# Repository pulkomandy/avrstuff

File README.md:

Various AVR (and other) stuff
=============================

This slightly messy repo is home to many of my electronics hacks and projects.

A wiki describing most of the stuff is at http://pulkomandy.tk/projects/avrstuff/ .

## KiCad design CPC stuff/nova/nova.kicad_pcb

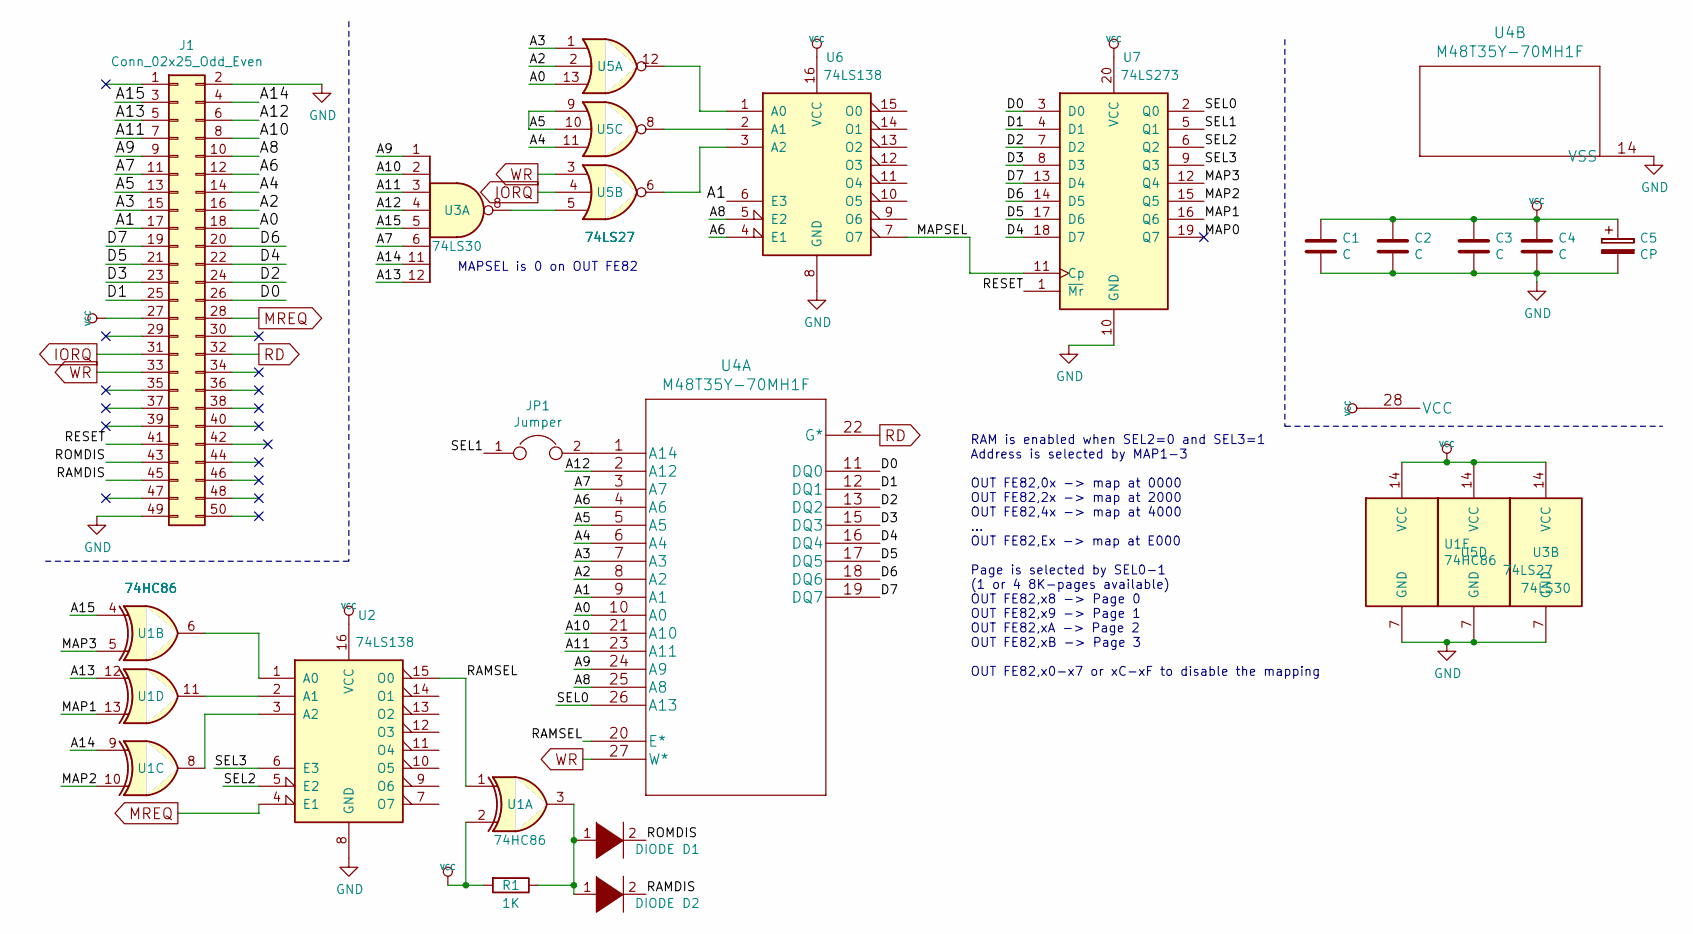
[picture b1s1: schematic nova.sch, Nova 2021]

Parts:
C1, C2, C3, C4: C; C_1206_3216Metric
C5: CP; CP_Radial_D5.0mm_P2.50mm
D1, D2: DIODE; D_SOD-123F
J1: Conn_02x25_Odd_Even; PinHeader_2x25_P2.54mm_Vertical
JP1: Jumper; SolderJumper-2_P1.3mm_Open_RoundedPad1.0x1.5mm
R1: 1K; R_0805_2012Metric
U1: 74HC86; SOIC-14_3.9x8.7mm_P1.27mm
U2, U6: 74LS138; SOIC-16_3.9x9.9mm_P1.27mm
U3: 74LS30; SOIC-14_3.9x8.7mm_P1.27mm
U4: M48T35Y-70MH1F
U5: 74LS27; SOIC-14_3.9x8.7mm_P1.27mm
U7: 74LS273; SOIC-20W_7.5x12.8mm_P1.27mm

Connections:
/A0: J1.18, U4.10 (A0), U5.13
/A1: J1.17, U4.9 (A1), U6.6 (E3)
/A2: J1.16, U4.8 (A2), U5.2
/A3: J1.15, U4.7 (A3), U5.1
/A4: J1.14, U4.6 (A4), U5.11
/A5: J1.13, U4.5 (A5), U5.9, U5.10
/A6: J1.12, U4.4 (A6), U6.4 (E1)
/A7: J1.11, U3.6, U4.3 (A7)
/A8: J1.10, U4.25 (A8), U6.5 (E2)
/A9: J1.9, U3.1, U4.24 (A9)
/A10: J1.8, U3.2, U4.21 (A10)
/A11: J1.7, U3.3, U4.23 (A11)
/A12: J1.6, U3.4, U4.2 (A12)
/A13: J1.5, U1.12, U3.12
/A14: J1.4, U1.9, U3.11
/A15: J1.3, U1.4, U3.5
/D0: J1.26, U4.11 (DQ0), U7.3 (D0)
/D1: J1.25, U4.12 (DQ1), U7.4 (D1)
/D2: J1.24, U4.13 (DQ2), U7.7 (D2)
/D3: J1.23, U4.15 (DQ3), U7.8 (D3)
/D4: J1.22, U4.16 (DQ4), U7.18 (D7)
/D5: J1.21, U4.17 (DQ5), U7.17 (D6)
/D6: J1.20, U4.18 (DQ6), U7.14 (D5)
/D7: J1.19, U4.19 (DQ7), U7.13 (D4)
/MAP1: U1.13, U7.16 (Q6)
/MAP2: U1.10, U7.15 (Q5)
/MAP3: U1.5, U7.12 (Q4)
/MAPSEL: U6.7 (O7), U7.11 (Cp)
/RAMDIS: D2.2 (A), J1.45
/RAMSEL: U1.1, U2.15 (O0), U4.20 (E*)
/RESET: J1.41, U7.1 (~Mr)
/ROMDIS: D1.2 (A), J1.43
/SEL0: U4.26 (A13), U7.2 (Q0)
/SEL1: JP1.1, U7.5 (Q1)
/SEL2: U2.5 (E2), U7.6 (Q2)
/SEL3: U2.6 (E3), U7.9 (Q3)
GND: C1.2, C2.2, C3.2, C4.2, C5.2, J1.2, J1.49, U1.7 (GND), U2.8 (GND), U3.7 (GND), U4.14 (VSS), U5.7 (GND), U6.8 (GND), U7.10 (GND)
IORQ: J1.31, U5.4
MREQ: J1.28, U2.4 (E1)
unnamed: D1.1 (K), D2.1 (K), R1.1, U1.3
unnamed: JP1.2, U4.1 (A14)
unnamed: U1.6, U2.1 (A0)
unnamed: U1.8, U2.3 (A2)
unnamed: U1.11, U2.2 (A1)
unnamed: U3.8, U5.5
unnamed: U5.6, U6.3 (A2)
unnamed: U5.8, U6.2 (A1)
unnamed: U5.12, U6.1 (A0)
RD: J1.32, U4.22 (G*)
VCC: C1.1, C2.1, C3.1, C4.1, C5.1, J1.27, R1.2, U1.2, U1.14 (VCC), U2.16 (VCC), U3.14 (VCC), U4.28 (VCC), U5.14 (VCC), U6.16 (VCC), U7.20 (VCC)
WR: J1.33, U4.27 (W*), U5.3

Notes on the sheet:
MAPSEL is 0 on OUT FE82
RAM is enabled when SEL2=0 and SEL3=1 Address is selected by MAP1-3 OUT FE82,0x -> map at 0000 OUT FE82,2x -> map at 2000 OUT FE82,4x -> map at 4000 ... OUT FE82,Ex -> map at E000 Page is selected by SEL0-1 (1 or 4 8K-pages available) OUT FE82,x8 -> Page 0 OUT FE82,x9 -> Page 1 OUT FE82,xA -> Page 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

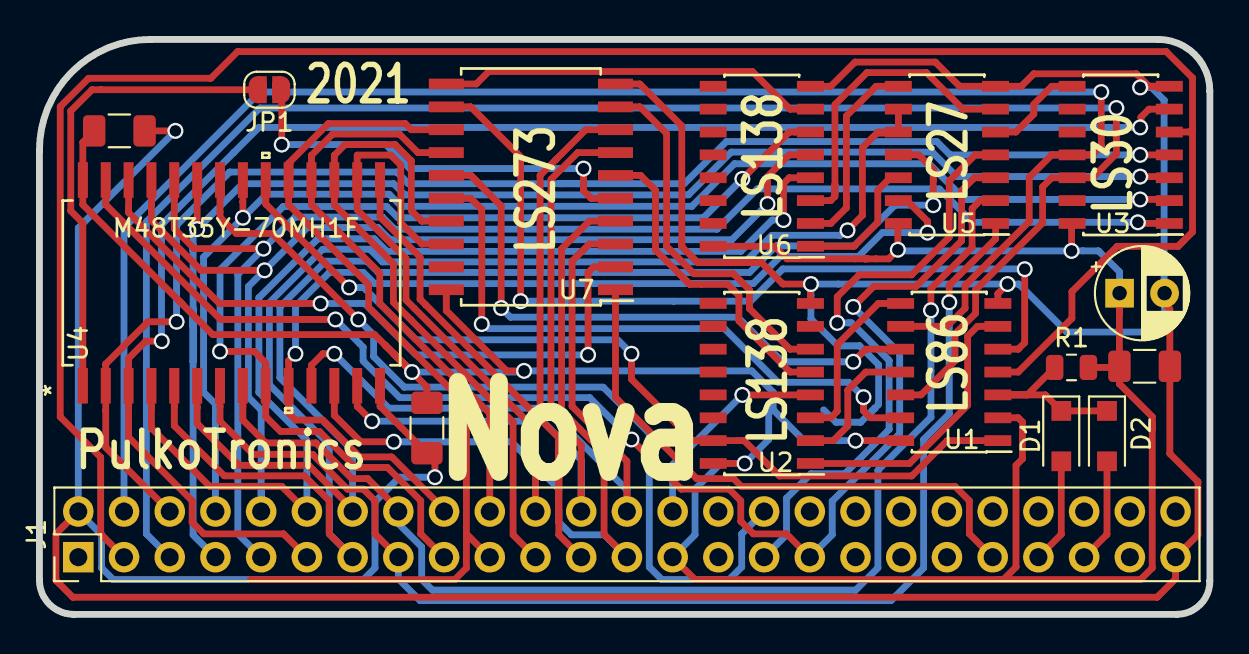
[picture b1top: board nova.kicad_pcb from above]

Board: 2 copper layers, 65.0 x 31.9 mm, 17 parts (0 on the bottom side), 51 nets.

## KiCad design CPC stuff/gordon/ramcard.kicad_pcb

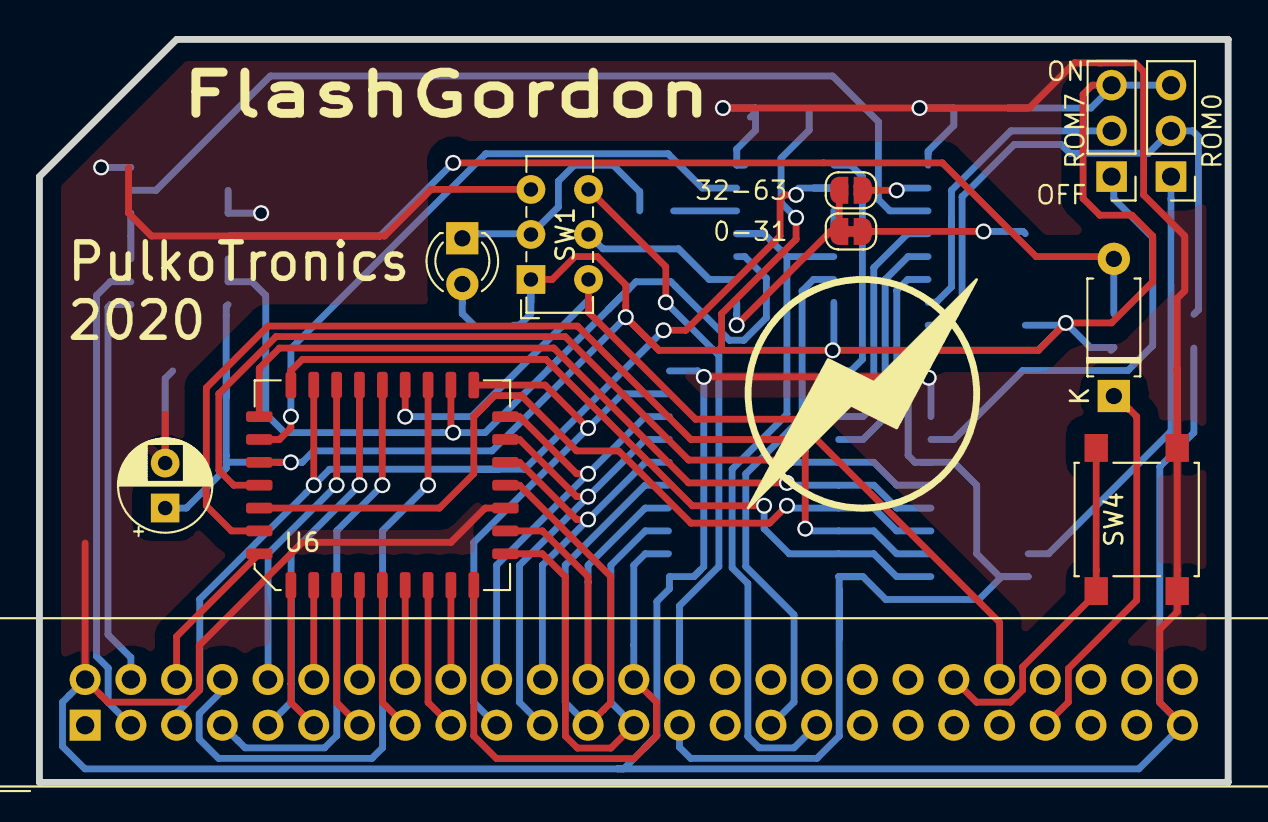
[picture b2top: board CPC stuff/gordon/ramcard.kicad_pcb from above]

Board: 2 copper layers, 66.0 x 41.3 mm, 23 parts (0 on the bottom side), 58 nets.

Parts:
1K, 1K#2: 1KR; R_0805_2012Metric
10K: 10KR; R_0805_2012Metric
220: 220R; R_0805_2012Metric
C2, C3, C4: C; C_1206_3216Metric_Pad1.42x1.75mm_HandSolder
C5: CP1; CP_Radial_D5.0mm_P2.50mm
D1: LED; LED_D3.0mm
D13: DIODE; D_A-405_P7.62mm_Horizontal
JP1, JP2: Jumper_3_Open; PinHeader_1x03_P2.54mm_Vertical
JP3: Jumper_NC_Small; SolderJumper-2_P1.3mm_Bridged_RoundedPad1.0x1.5mm
JP4: Jumper_NO_Small; SolderJumper-2_P1.3mm_Open_RoundedPad1.0x1.5mm
P1: CONN_25X2; IDC-Header_2x25_P2.54mm_Vertical
SW1: WRITE; SW_E-Switch_EG1271_DPDT
SW4: SW_PUSH; SW_SPST_B3S-1000
U1: 74LS574; SOIC-20W_7.5x12.8mm_P1.27mm
U2: 74LS32; SOIC-14_3.9x8.7mm_P1.27mm
U3, U5: 74LS138; SOIC-16_3.9x9.9mm_P1.27mm
U4: 74LS00; SOIC-14_3.9x8.7mm_P1.27mm
U6: 29C040; PLCC-32_11.4x14.0mm_P1.27mm

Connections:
//CE: U2.3, U4.12, U4.13, U6.22
//WE: U2.6, U6.31
/A0: P1.18, U6.12
/A1: P1.17, U6.11
/A2: P1.16, U6.10
/A3: P1.15, U6.9
/A4: P1.14, U6.8
/A5: P1.13, U6.7
/A6: P1.12, U6.6
/A7: P1.11, U6.5
/A8: P1.10, U6.27
/A9: P1.9, U6.26
/A10: P1.8, U6.23
/A11: P1.7, U6.25
/A12: P1.6, U6.4
/A13: P1.5, U2.9, U6.28
/A14: P1.4, U4.1
/A14A15: U4.6, U5.6
/A15: P1.3, U4.2
/BUSRESET: P1.40, SW4.1
/D0: P1.26, U1.2, U6.13
/D1: P1.25, U1.3, U6.14
/D2: P1.24, U1.4, U6.15
/D3: P1.23, U1.5, U6.17
/D4: P1.22, U1.6, U6.18
/D5: P1.21, U1.7, U6.19
/D6: P1.20, U1.8, U6.20
/D7: P1.19, U1.9, U6.21
/Q0: U1.19, U3.1, U6.29
/Q1: U1.18, U3.2, U6.3
/Q2: U1.17, U3.3, U6.2
/Q3: U1.16, U3.4, U6.30
/Q4: U1.15, U3.5, U6.1
/Q5: U1.14, U5.3
/Q6: U1.13, U5.4
/Q7: U1.12, U5.5
/R0EN: 10K.1, JP2.2, U5.1
/R7EN: JP1.2, U5.2
/RDWR: SW1.5, U2.2
/ROMACC: JP3.2, JP4.2, U2.1
GND: 10K.2, C2.2, C3.2, C4.2, C5.2, P1.2, P1.49, SW1.3, SW4.2, U1.1, U1.10, U2.7, U3.8, U4.7, U4.9, U4.10, U5.8, U6.16
IORQ: P1.31, U2.13
MREQ: P1.28, SW1.6
unnamed: 220.1, D1.1, SW1.2
unnamed: 1K.2, D1.2
unnamed: 1K#2.1, D13.2, U4.11
unnamed: JP1.1, U3.7
unnamed: JP2.1, U3.15
unnamed: JP3.1, U5.12
unnamed: JP4.1, U5.7
unnamed: 220.2, U2.5
unnamed: U2.10, U2.11
unnamed: U4.3, U4.4, U4.5
ROMDIS: D13.1, P1.43
ROMEN: P1.42, SW1.4, U6.24
ROMSEL: U1.11, U2.8
VCC: 1K.1, 1K#2.2, C2.1, C3.1, C4.1, C5.1, JP1.3, JP2.3, P1.27, SW1.1, U1.20, U2.14, U3.6, U3.16, U4.14, U5.16, U6.32
WR: P1.33, U2.4, U2.12

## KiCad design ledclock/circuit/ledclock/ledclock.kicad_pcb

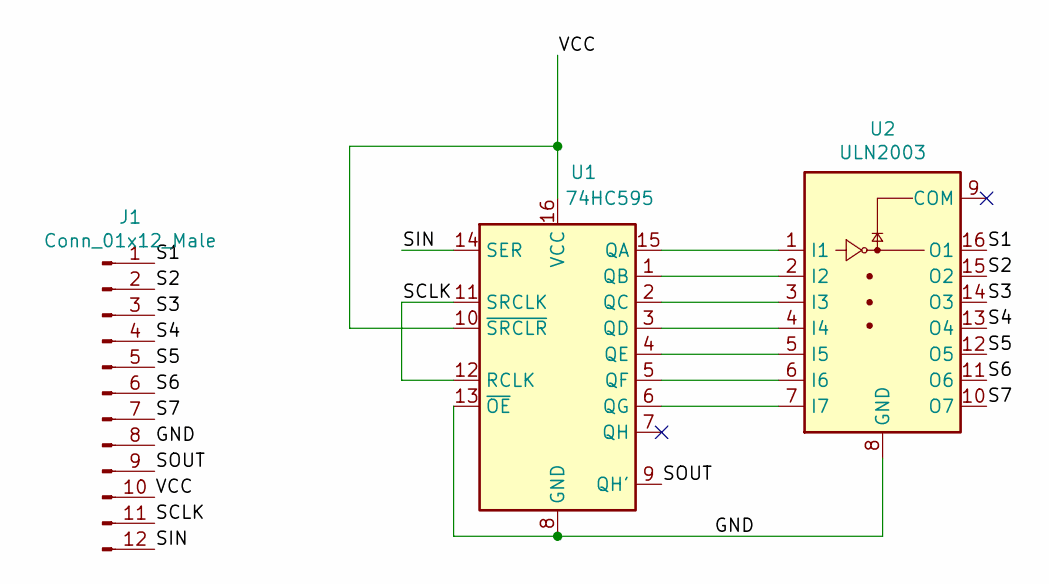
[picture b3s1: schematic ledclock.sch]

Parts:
J1: Conn_01x12_Male; TE_MicroMatch_215750-0016_2x08_P1.27mm_Vertical
U1: 74HC595; DIP-16_W7.62mm
U2: ULN2003; SOIC-16_3.9x9.9mm_P1.27mm

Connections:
/GND: J1.8, U1.8 (GND), U1.13 (~OE), U2.8 (GND)
/S1: J1.1, U2.16 (O1)
/S2: J1.2, U2.15 (O2)
/S3: J1.3, U2.14 (O3)
/S4: J1.4, U2.13 (O4)
/S5: J1.5, U2.12 (O5)
/S6: J1.6, U2.11 (O6)
/S7: J1.7, U2.10 (O7)
/SCLK: J1.11, U1.11 (SRCLK), U1.12 (RCLK)
/SIN: J1.12, U1.14 (SER)
/SOUT: J1.9, U1.9 (QH')
/VCC: J1.10, U1.10 (~SRCLR), U1.16 (VCC)
unnamed: U1.1 (QB), U2.2 (I2)
unnamed: U1.2 (QC), U2.3 (I3)
unnamed: U1.3 (QD), U2.4 (I4)
unnamed: U1.4 (QE), U2.5 (I5)
unnamed: U1.5 (QF), U2.6 (I6)
unnamed: U1.6 (QG), U2.7 (I7)
unnamed: U1.15 (QA), U2.1 (I1)

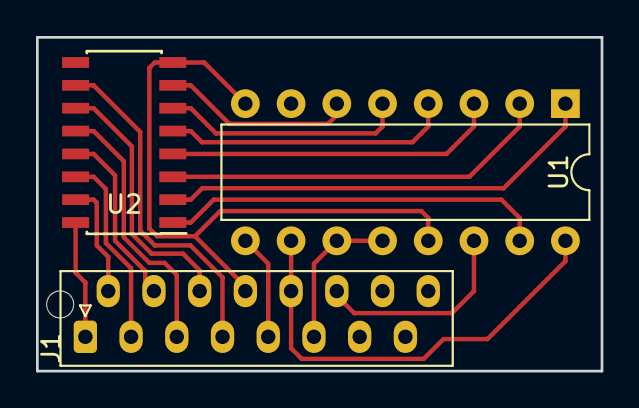
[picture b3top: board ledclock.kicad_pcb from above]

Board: 2 copper layers, 31.4 x 18.5 mm, 3 parts (0 on the bottom side), 19 nets.

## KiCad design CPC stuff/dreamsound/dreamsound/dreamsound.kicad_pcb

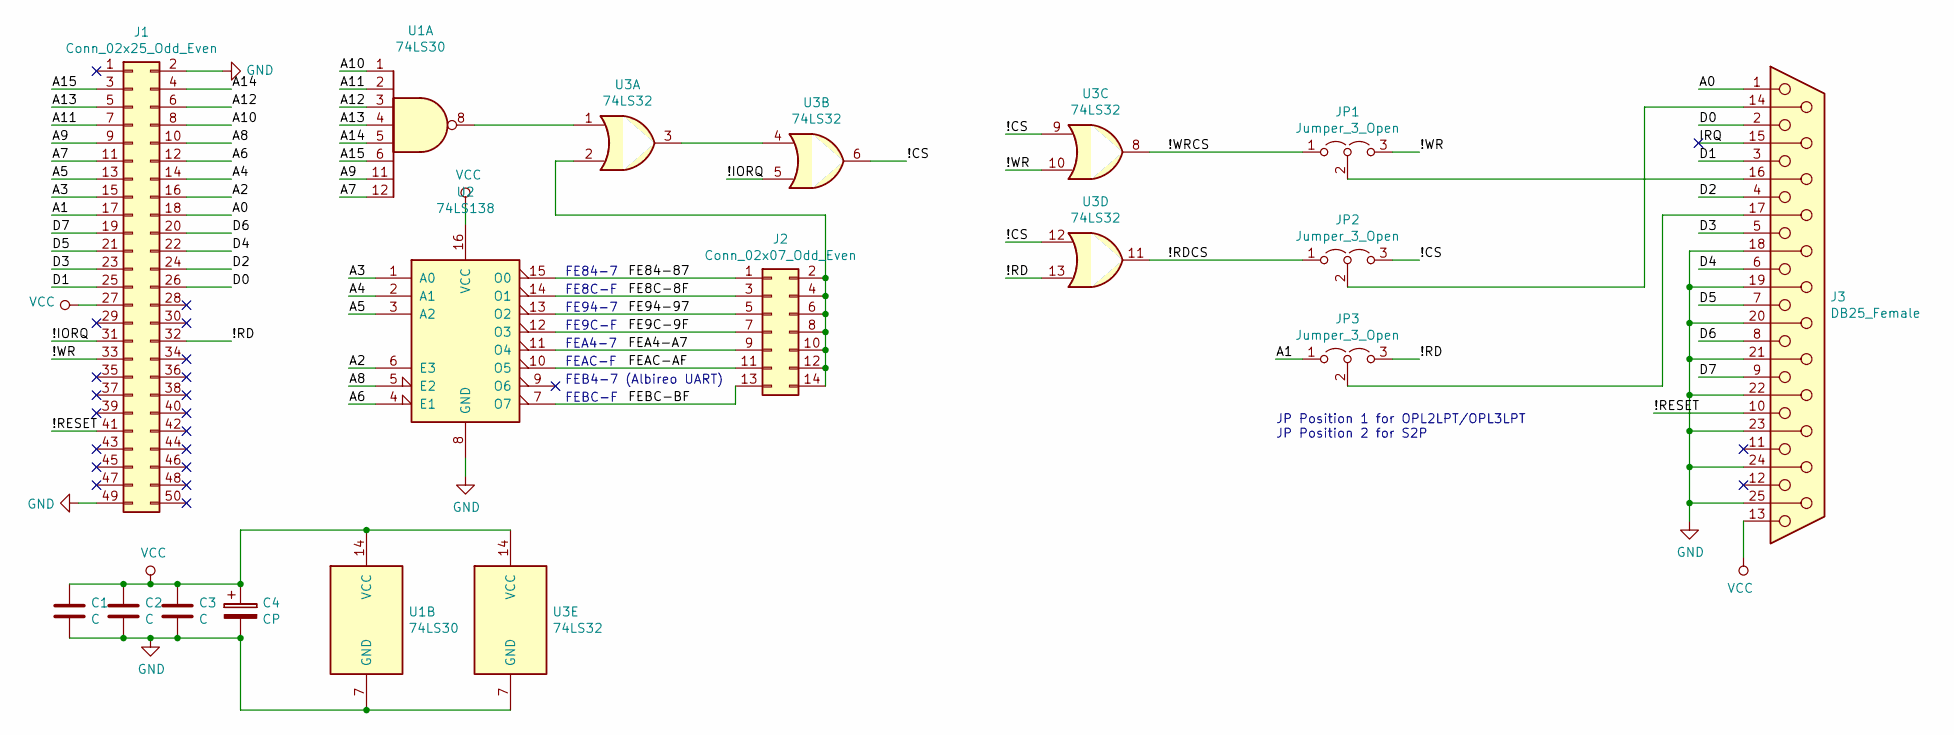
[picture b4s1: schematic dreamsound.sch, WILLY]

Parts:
C1, C2, C3: C; C_1206_3216Metric_Pad1.42x1.75mm_HandSolder
C4: CP; CP_Radial_D5.0mm_P2.50mm
J1: Conn_02x25_Odd_Even; IDC-Header_2x25_P2.54mm_Vertical
J2: Conn_02x07_Odd_Even; PinHeader_2x07_P2.54mm_Vertical
J3: DB25_Female; DSUB-25_Female_Horizontal_P2.77x2.84mm_EdgePinOffset4.94mm_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
JP1, JP2, JP3: Jumper_3_Open; PinHeader_1x03_P2.54mm_Vertical
U1: 74LS30; SOIC-14_3.9x8.7mm_P1.27mm
U2: 74LS138; SOIC-16_3.9x9.9mm_P1.27mm
U3: 74LS32; SOIC-14_3.9x8.7mm_P1.27mm

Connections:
/!CS: JP2.3 (B), U3.6, U3.9, U3.12
/!IORQ: J1.31, U3.5
/!RD: J1.32, JP3.3 (B), U3.13
/!RDCS: JP2.1 (A), U3.11
/!RESET: J1.41, J3.10
/!WR: J1.33, JP1.3 (B), U3.10
/!WRCS: JP1.1 (A), U3.8
/A0: J1.18, J3.1
/A1: J1.17, JP3.1 (A)
/A2: J1.16, U2.6 (E3)
/A3: J1.15, U2.1 (A0)
/A4: J1.14, U2.2 (A1)
/A5: J1.13, U2.3 (A2)
/A6: J1.12, U2.4 (E1)
/A7: J1.11, U1.12
/A8: J1.10, U2.5 (E2)
/A9: J1.9, U1.11
/A10: J1.8, U1.1
/A11: J1.7, U1.2
/A12: J1.6, U1.3
/A13: J1.5, U1.4
/A14: J1.4, U1.5
/A15: J1.3, U1.6
/D0: J1.26, J3.2
/D1: J1.25, J3.3
/D2: J1.24, J3.4
/D3: J1.23, J3.5
/D4: J1.22, J3.6
/D5: J1.21, J3.7
/D6: J1.20, J3.8
/D7: J1.19, J3.9
/FE8C-8F: J2.3, U2.14 (O1)
/FE9C-9F: J2.7, U2.12 (O3)
/FE84-87: J2.1, U2.15 (O0)
/FE94-97: J2.5, U2.13 (O2)
/FEA4-A7: J2.9, U2.11 (O4)
/FEAC-AF: J2.11, U2.10 (O5)
/FEBC-BF: J2.13, U2.7 (O7)
GND: C1.2, C2.2, C3.2, C4.2, J1.2, J1.49, J3.18, J3.19, J3.20, J3.21, J3.22, J3.23, J3.24, J3.25, U1.7 (GND), U2.8 (GND), U3.7 (GND)
unnamed: J2.2, J2.4, J2.6, J2.8, J2.10, J2.12, J2.14, U3.2
unnamed: J3.14, JP2.2 (C)
unnamed: J3.16, JP1.2 (C)
unnamed: J3.17, JP3.2 (C)
unnamed: U1.8, U3.1
unnamed: U3.3, U3.4
VCC: C1.1, C2.1, C3.1, C4.1, J1.27, J3.13, U1.14 (VCC), U2.16 (VCC), U3.14 (VCC)

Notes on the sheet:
FE84-7
FE8C-F
FE94-7
FE9C-F
FEA4-7
FEAC-F
FEB4-7 (Albireo UART)
FEBC-F
JP Position 1 for OPL2LPT/OPL3LPT JP Position 2 for S2P

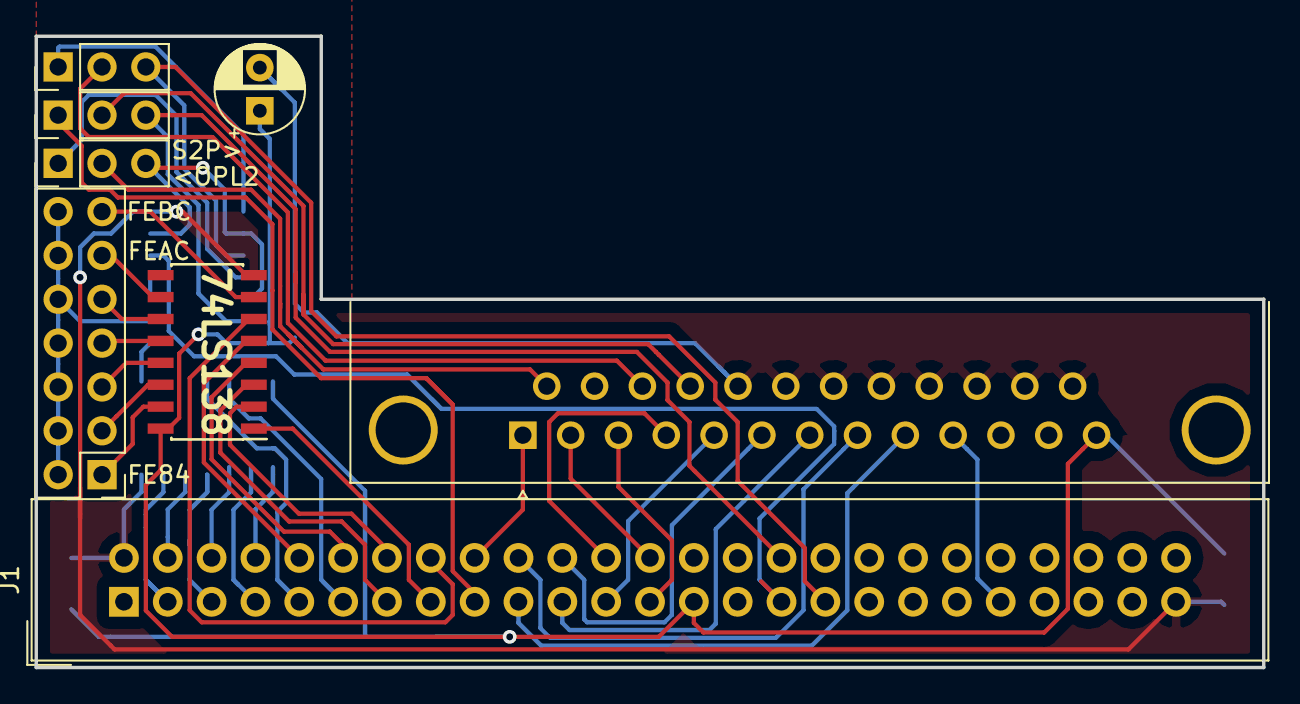
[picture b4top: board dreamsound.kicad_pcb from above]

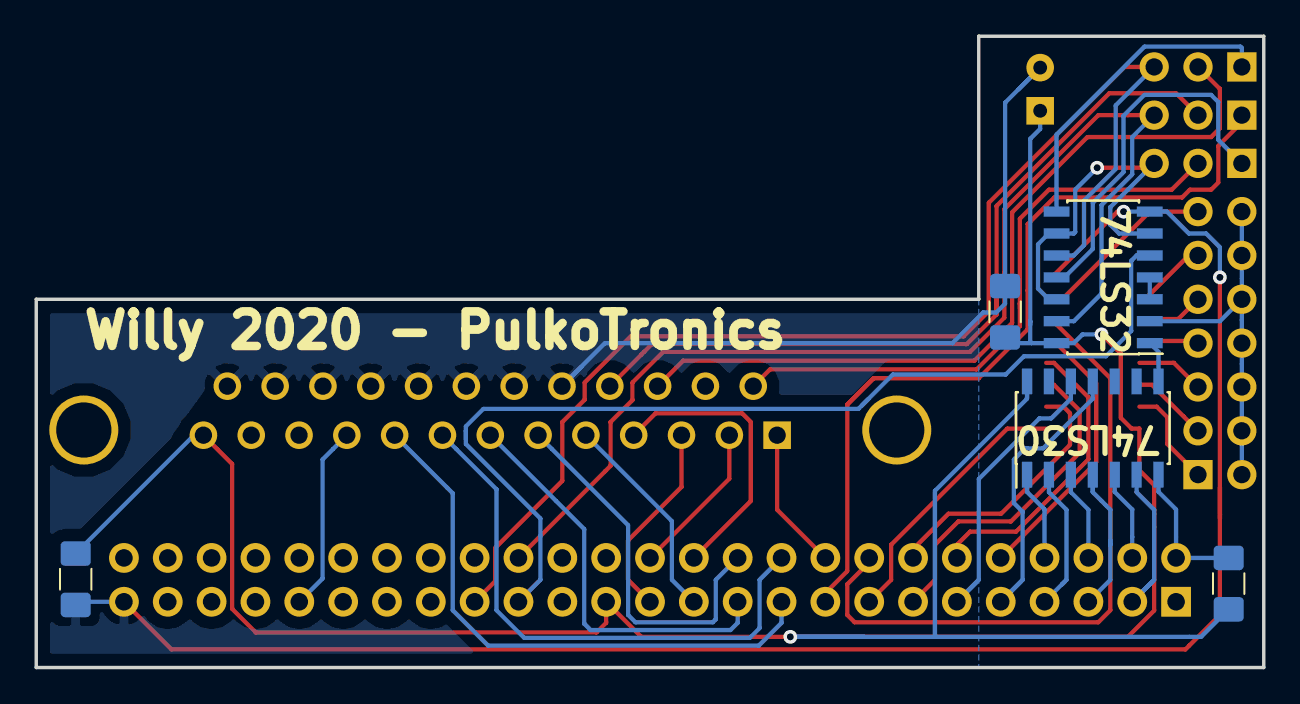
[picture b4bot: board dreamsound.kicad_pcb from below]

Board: 2 copper layers, 71.1 x 36.6 mm, 13 parts (5 on the bottom side), 46 nets.

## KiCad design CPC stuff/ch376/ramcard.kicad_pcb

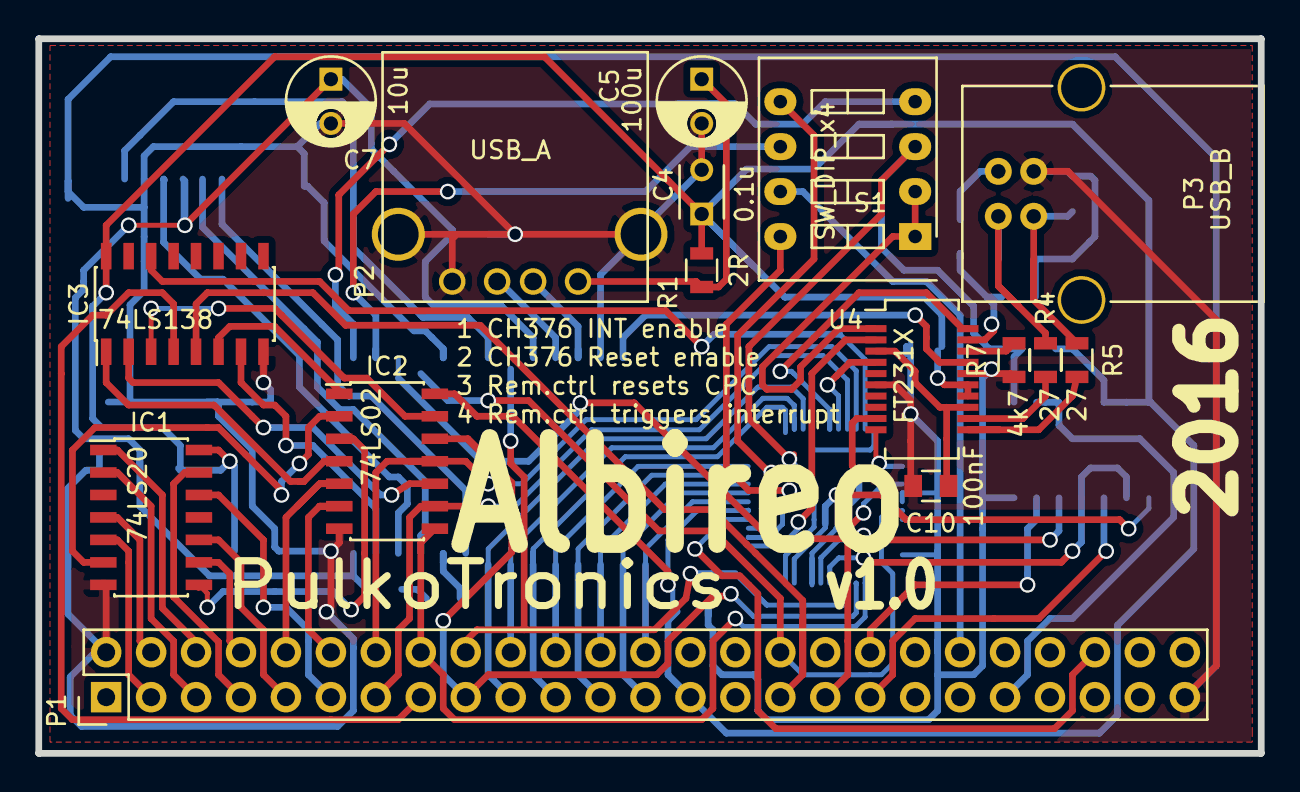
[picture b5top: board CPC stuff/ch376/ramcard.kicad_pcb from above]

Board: 2 copper layers, 69.1 x 40.4 mm, 32 parts (0 on the bottom side), 76 nets.

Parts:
C1, C2, C3: 1uF; C_0805
C4: 0.1u; C_Disc_D3_P2.5
C5: 100u; C_Radial_D5_L6_P2.5
C6: 10nF; C_0805
C7: 10u; C_Radial_D5_L6_P2.5
C8, C9: 47pF; C_0805
C10: 100nF; C_0805
D1: LED; R_0805
IC1: 74LS20; SOIC-14_3.9x8.7mm_Pitch1.27mm
IC2: 74LS02; SOIC-14_3.9x8.7mm_Pitch1.27mm
IC3: 74LS138; SOIC-16_3.9x9.9mm_Pitch1.27mm
IC4: CH376; CH376_SOJ28
P1: CONN_25X2; Pin_Header_Straight_2x25
P2: USB_A
P3: USB_B
R1: 2R; R_0805
R2, R7: 4k7; R_0805
R3: 10k; R_0805
R4, R5: 27; R_0805
R6: 4K7; R_0805
R8: 1K; R_0805
S1: SW_DIP_x4; SW_DIP_x4_Slide
U1: LD1117S33CTR; SOT-223
U2: CONN_microSD; Memory_Card_microSD_DM3CS-SF
U3: TL16C550C; TQFP-48_7x7mm_Pitch0.5mm
U4: FT231X; SSOP-24_3.9x8.7mm_Pitch0.635mm
U5: 74LS38; SOIC-14_3.9x8.7mm_Pitch1.27mm

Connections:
+3V3: C6.1, C7.1, D1.2, IC4.9, IC4.28, U1.2, U2.4
/12MHz: IC4.13, U4.17
/24MHz: U3.14, U4.10
//CTS: U3.38, U4.2
//DCD: S1.5, U3.40
//DSR: S1.8, U3.39
//INT: P1.35, U5.3
//IORQ: IC3.5, P1.31
//NMI: P1.36, U5.6
//OUT1: U3.34, U5.1
//OUT2: U3.31, U5.5
//RD: IC4.4, P1.32, U3.19
//RESET: P1.41, U5.9, U5.10
//RTS: U3.32, U4.9
//SD_CS: IC4.23, U2.2
//WR: IC4.3, P1.33, U3.16
/A0: IC4.8, P1.18, U3.28
/A1: IC2.12, P1.17, U3.27
/A2: IC2.8, P1.16, U3.26
/A3: IC3.4, P1.15
/A4: IC2.11, P1.14, U3.10
/A5: IC2.9, P1.13, U3.9
/A6: IC2.6, P1.12
/A7: IC1.12, P1.11
/A8: IC2.5, P1.10
/A9: IC1.10, P1.9
/A10: IC1.9, P1.8
/A11: IC1.13, P1.7
/A12: IC1.1, P1.6
/A13: IC1.2, P1.5
/A14: IC1.4, P1.4
/A15: IC1.5, P1.3
/AWAKE: R7.2, U4.18
/BUSRST: P1.40, S1.7
/CE1: IC2.1, IC3.6
/CURSOR: P1.46, U3.41
/D0: IC4.15, P1.26, U3.43
/D1: IC4.16, P1.25, U3.44
/D2: IC4.17, P1.24, U3.45
/D3: IC4.18, P1.23, U3.46
/D4: IC4.19, P1.22, U3.47
/D5: IC4.20, P1.21, U3.2
/D6: IC4.21, P1.20, U3.3
/D7: IC4.22, P1.19, U3.4
/FE80: IC3.7, IC4.27
/FEBx: IC3.14, U3.11
/GPO2: S1.1, S1.2, U4.1
/INT: IC4.1, S1.4
/INTRPT: U3.30, U5.2, U5.4
/PRESET: R6.2, S1.3, U3.35, U5.8
/RSTI: IC4.2, S1.6
/RX: U3.7, U4.20
/SD_CLK: IC4.26, U2.5
/SD_DI: IC4.25, U2.3
/SD_DO: IC4.7, U2.7
/TX: U3.8, U4.4
/VBUS_Sense: R2.2, R3.1, U4.19
GND: C1.2, C2.2, C3.2, C4.2, C5.2, C6.2, C7.2, C8.2, C9.2, C10.2, IC1.7, IC2.7, IC3.8, IC4.5, IC4.12, P1.2, P1.49, P2.4, P2.5, P3.4, R3.2, R7.1, U1.1, U2.6, U2.9, U3.17, U3.18, U3.20, U3.24, U4.6, U4.16, U5.7
unnamed: C5.1, P2.1, R1.1
unnamed: C8.1, P3.3, R5.2
unnamed: C9.1, P3.2, R4.2
unnamed: C10.1, U4.3, U4.13
unnamed: D1.1, R8.2
unnamed: IC1.6, IC2.2
unnamed: IC1.8, IC2.3
unnamed: IC2.4, IC3.1
unnamed: IC2.10, IC3.2
unnamed: IC2.13, IC3.3
unnamed: IC4.10, P2.3
unnamed: IC4.11, P2.2
unnamed: IC4.24, R8.1
unnamed: P3.1, R2.1
unnamed: R4.1, U4.12
unnamed: R5.1, U4.11
unnamed: U3.5, U3.12
VCC: C1.1, C2.1, C3.1, C4.1, IC1.14, IC2.14, IC3.16, P1.27, R1.2, R6.1, U1.3, U3.42, U4.14, U4.15, U5.12, U5.13, U5.14

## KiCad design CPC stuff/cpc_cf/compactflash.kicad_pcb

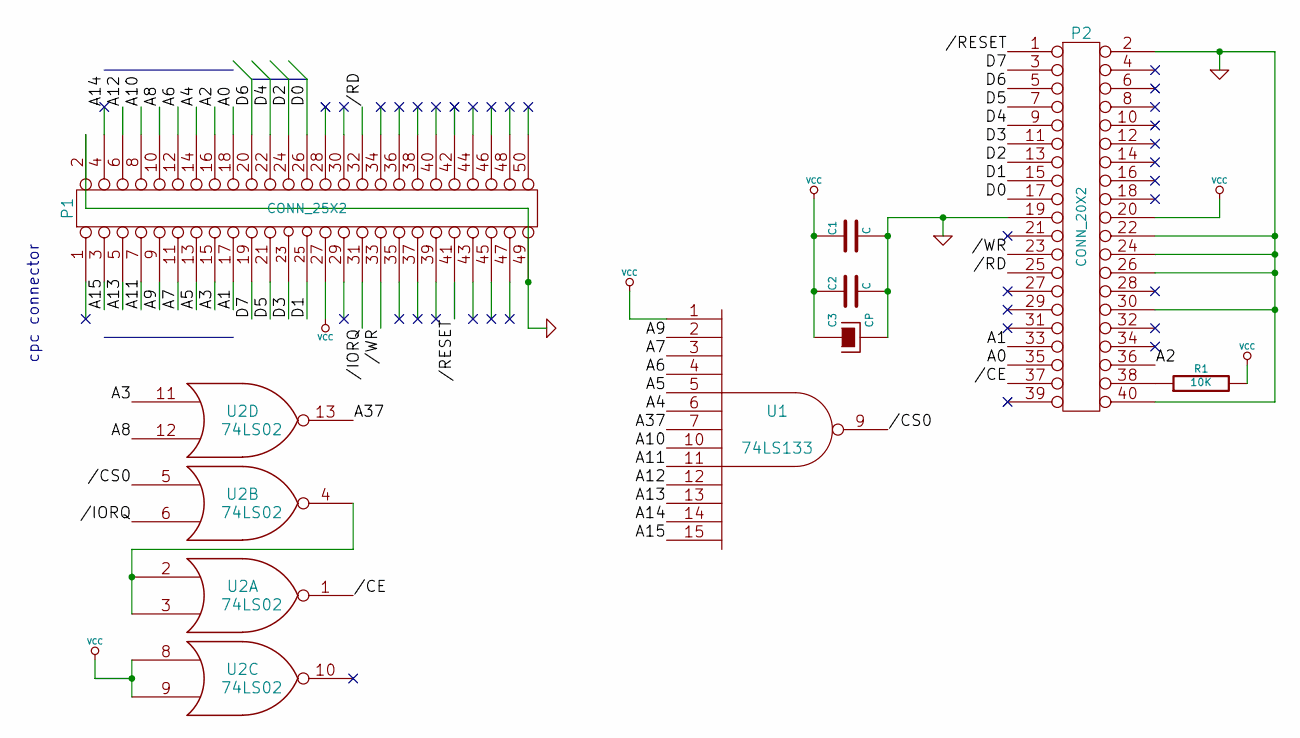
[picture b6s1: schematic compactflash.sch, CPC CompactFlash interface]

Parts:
C1, C2: C
C3: CP
P1: CONN_25X2
P2: CONN_20X2
R1: 10K
U1: 74LS133
U2: 74LS02

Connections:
//CE: P2.37, U2.1
//CS0: U1.9, U2.5
//IORQ: P1.31, U2.6
//RD: P1.32, P2.25
//RESET: P1.41, P2.1
//WR: P1.33, P2.23
/A0: P1.18, P2.35
/A1: P1.17, P2.33
/A2: P1.16, P2.36
/A3: P1.15, U2.11
/A4: P1.14, U1.6
/A5: P1.13, U1.5
/A6: P1.12, U1.4
/A7: P1.11, U1.3
/A8: P1.10, U2.12
/A9: P1.9, U1.2
/A10: P1.8, U1.10
/A11: P1.7, U1.11
/A12: P1.6, U1.12
/A13: P1.5, U1.13
/A14: P1.4, U1.14
/A15: P1.3, U1.15
/A37: U1.7, U2.13
/D0: P1.26, P2.17
/D1: P1.25, P2.15
/D2: P1.24, P2.13
/D3: P1.23, P2.11
/D4: P1.22, P2.9
/D5: P1.21, P2.7
/D6: P1.20, P2.5
/D7: P1.19, P2.3
GND: C1.2, C2.2, C3.2, P1.2, P1.49, P2.2, P2.19, P2.22, P2.24, P2.26, P2.30, P2.40, U1.8 (GND), U2.7 (GND)
unnamed: U2.2, U2.3, U2.4
unnamed: P2.38, R1.1
VCC: C1.1, C2.1, C3.1, P1.27, P2.20, R1.2, U1.1, U1.16 (VCC), U2.8, U2.9, U2.14 (VCC)

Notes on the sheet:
cpc connector

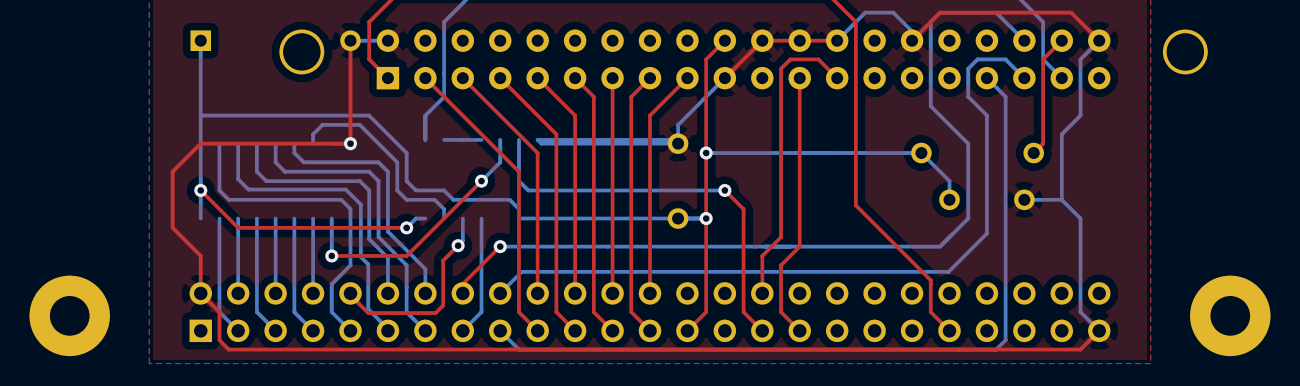
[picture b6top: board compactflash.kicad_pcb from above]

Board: 2 copper layers, 8 parts (0 on the bottom side), 35 nets.

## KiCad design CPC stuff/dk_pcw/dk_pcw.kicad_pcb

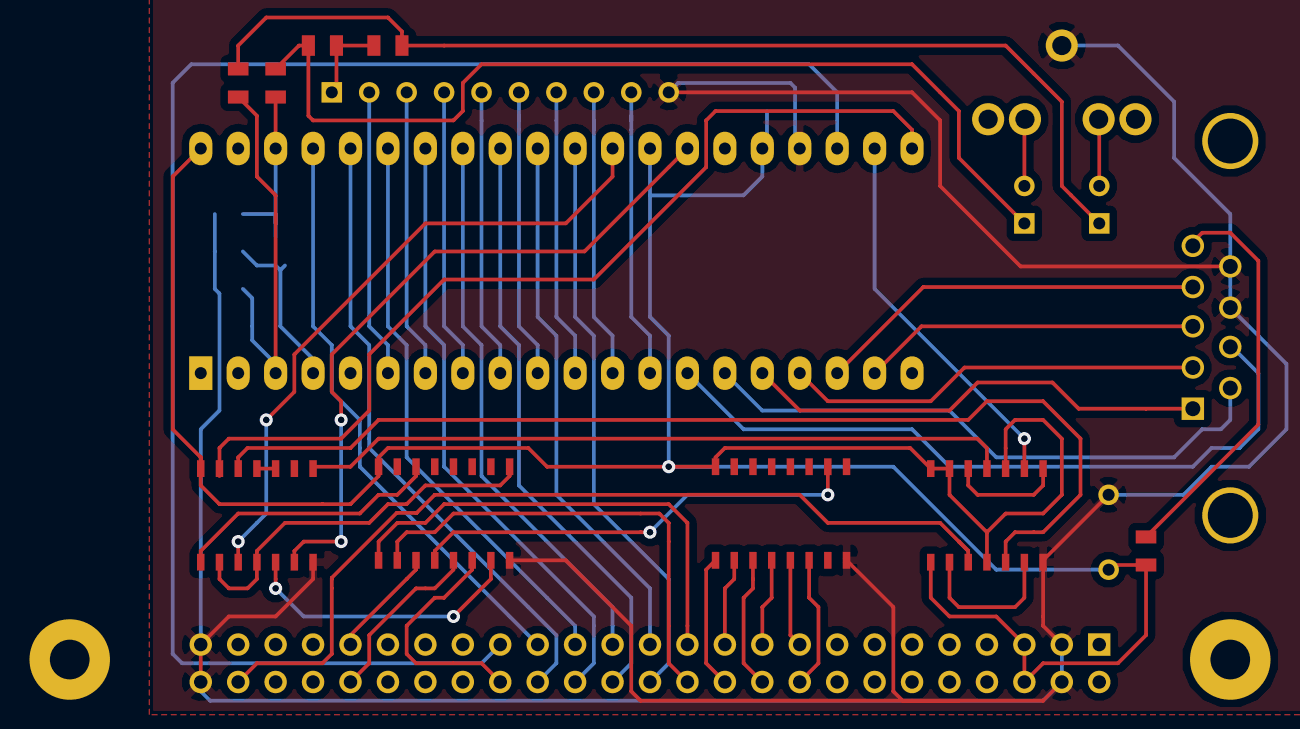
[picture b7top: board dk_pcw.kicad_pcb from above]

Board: 2 copper layers, 23 parts (0 on the bottom side), 59 nets.

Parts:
C1: 10u; C2
C2: 10n; SM0805
C3, C4: C; C1V5
J1: CONN_25X2; HE10_50D
J3: AUDIO-JACK2; SparkFun-AUDIO-JACK
J4: DB9; DB9MC
R1, R11, R12, R13, R14, R15, R16, R17, R18, R19: R; SM0805
RR1: RR9; SIL-10
U1, U4: 74LS138; SO16N
U2: 74LS74; SO14N
U3: 74LS00; SO14N
U5: AY3-8910; DIP-40__600_ELL

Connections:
//IOREQ: J1.42, U4.5
//M1: J1.34, U4.6
//RD: J1.41, U4.3
//RESET: J1.33, U5.23
/A0: J1.23, U4.1
/A1: J1.24, U4.2
/A2: J1.21, U1.2
/A3: J1.22, U1.1
/A4: J1.19, U1.4
/A5: J1.20, U1.3
/A6: J1.17, U1.5
/A7: J1.18, U1.6
/AUDA: R12.2, R14.2, R15.2, U5.3
/AUDB: R13.2, R14.1, R16.1, U5.4
/AUDC: R11.2, R16.2, R17.1, U5.38
/BC1: U3.3, U5.29
/BDIR: U3.6, U5.27
/CLK1: U2.9, U5.22
/CLK2: U2.5, U3.12
/CLK24: U2.11, U3.8
/D0: J1.31, U5.37
/D1: J1.32, U5.36
/D2: J1.29, U5.35
/D3: J1.30, U5.34
/D4: J1.27, U5.33
/D5: J1.28, U5.32
/D6: J1.25, U5.31
/D7: J1.26, U5.30
/DAC: R18.1, R19.1, RR1.1
/IOA0: U3.13, U5.21
/IOA2: J4.3, U5.19
/IOA3: J4.4, U5.18
/IOA4: J4.2, U5.17
/IOA5: J4.1, U5.16
/IOA6: J4.6, U5.15
/IOA7: J4.7, U5.14
/IOB0: RR1.9, U5.13
/IOB1: RR1.8, U5.12
/IOB2: RR1.7, U5.11
/IOB3: RR1.6, U5.10
/IOB4: RR1.5, U5.9
/IOB5: RR1.4, U5.8
/IOB6: RR1.3, U5.7
/IOB7: RR1.2, U5.6
/LEFT: C3.2, J3.3
/RIGHT: C4.2, J3.4
/Z80CLK: J1.48, U2.3
GND: C1.2, C2.2, J1.3, J1.4, J1.49, J1.50, J3.1, J4.8, J4.9, R11.1, R12.1, R13.1, RR1.10, U1.8, U2.7, U3.7, U4.8, U5.24
unnamed: C4.1, R17.2, R19.2
unnamed: C3.1, R15.1, R18.2
unnamed: U2.8, U2.12
unnamed: U2.2, U2.6
unnamed: U3.1, U4.14
unnamed: U3.2, U3.4, U4.9
unnamed: U3.5, U4.7
unnamed: U3.10, U3.11
unnamed: U1.10, U4.4
unnamed: J4.5, R1.2
VCC: C1.1, C2.1, J1.5, J1.6, R1.1, U1.16, U2.1, U2.4, U2.10, U2.13, U2.14, U3.14, U4.16, U5.25, U5.28, U5.40

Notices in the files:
parts and their libraries:
Copyright 2016 Accelerated Designs. All rights reserved.
